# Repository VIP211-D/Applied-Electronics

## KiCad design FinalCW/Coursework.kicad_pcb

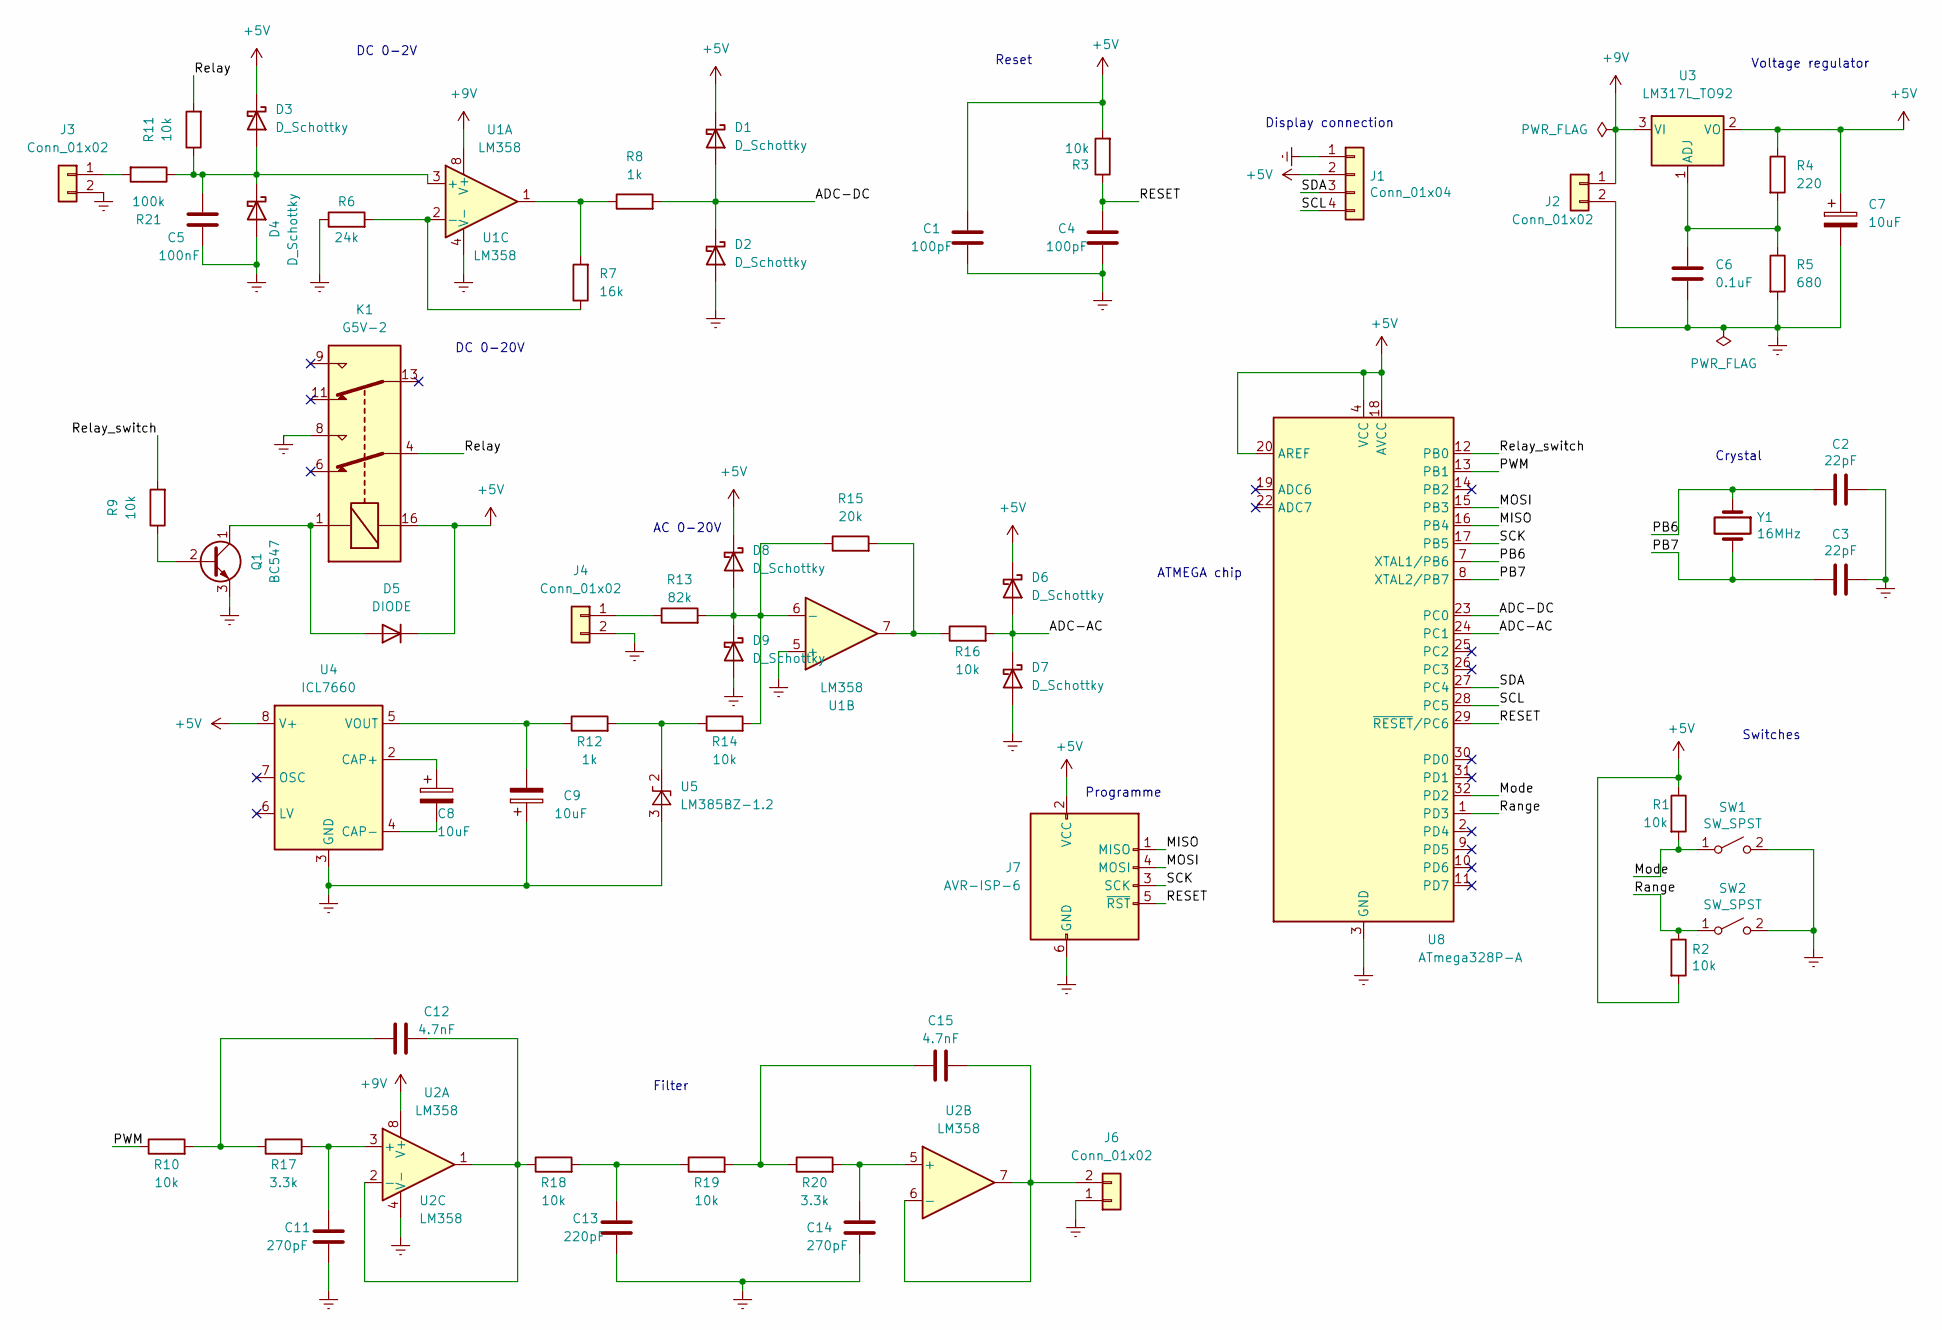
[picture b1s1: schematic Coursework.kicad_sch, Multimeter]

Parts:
C1, C4: 100pF; C_Disc_D3.0mm_W1.6mm_P2.50mm
C2, C3: 22pF; C_0805_2012Metric_Pad1.18x1.45mm_HandSolder
C5: 100nF; C_Disc_D3.0mm_W1.6mm_P2.50mm
C6: 0.1uF; C_Disc_D3.0mm_W1.6mm_P2.50mm
C7, C8, C9: 10uF; CP_Radial_D5.0mm_P2.50mm
C11, C14: 270pF; C_Disc_D3.0mm_W1.6mm_P2.50mm
C12, C15: 4.7nF; C_Disc_D3.0mm_W1.6mm_P2.50mm
C13: 220pF; C_Disc_D3.0mm_W1.6mm_P2.50mm
D1, D2, D3, D4, D6, D7, D8, D9: D_Schottky; D_DO-35_SOD27_P7.62mm_Horizontal
D5: DIODE; D_DO-41_SOD81_P10.16mm_Horizontal
J1: Conn_01x04; PinHeader_1x04_P2.54mm_Horizontal
J2, J3, J4, J6: Conn_01x02; PinHeader_1x02_P2.54mm_Vertical
J7: AVR-ISP-6; PinHeader_2x03_P2.54mm_Vertical
K1: G5V-2; Relay_DPDT_Omron_G5V-2
Q1: BC547; TO-92_Inline
R1, R2, R3, R9, R10, R11, R14, R16, R18, R19: 10k; R_Axial_DIN0207_L6.3mm_D2.5mm_P10.16mm_Horizontal
R4: 220; R_Axial_DIN0207_L6.3mm_D2.5mm_P10.16mm_Horizontal
R5: 680; R_Axial_DIN0207_L6.3mm_D2.5mm_P10.16mm_Horizontal
R6: 24k; R_Axial_DIN0207_L6.3mm_D2.5mm_P10.16mm_Horizontal
R7: 16k; R_Axial_DIN0207_L6.3mm_D2.5mm_P10.16mm_Horizontal
R8, R12: 1k; R_Axial_DIN0207_L6.3mm_D2.5mm_P10.16mm_Horizontal
R13: 82k; R_Axial_DIN0207_L6.3mm_D2.5mm_P10.16mm_Horizontal
R15: 20k; R_Axial_DIN0207_L6.3mm_D2.5mm_P10.16mm_Horizontal
R17, R20: 3.3k; R_Axial_DIN0207_L6.3mm_D2.5mm_P10.16mm_Horizontal
R21: 100k; R_Axial_DIN0207_L6.3mm_D2.5mm_P10.16mm_Horizontal
SW1, SW2: SW_SPST; SW_PUSH_6mm_H5mm
U1, U2: LM358; DIP-8_W7.62mm_LongPads
U3: LM317L_TO92; TO-220-3_Vertical
U4: ICL7660; DIP-8_W10.16mm_LongPads
U5: LM385BZ-1.2; TO-92_Inline
U8: ATmega328P-A; TQFP-32_7x7mm_P0.8mm
Y1: 16MHz; Crystal_SMD_HC49-SD

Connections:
+5V: C1.1, C7.1, D1.1 (K), D3.1 (K), D5.2 (K), D6.1 (K), D8.1 (K), J1.2, J7.2 (VCC), K1.16, R1.1, R2.2, R3.2, R4.1, U3.2 (VO), U4.8 (V+), U8.4 (VCC), U8.6 (VCC), U8.18 (AVCC), U8.20 (AREF)
+9V: J2.1, U1.8 (V+), U2.8 (V+), U3.3 (VI)
/ADC-AC: D6.2 (A), D7.1 (K), R16.2, U8.24 (PC1)
/ADC-DC: D1.2 (A), D2.1 (K), R8.2, U8.23 (PC0)
/MISO: J7.1 (MISO), U8.16 (PB4)
/MOSI: J7.4 (MOSI), U8.15 (PB3)
/Mode: R1.2, SW1.1 (A), U8.32 (PD2)
/PB6: C2.1, U8.7 (XTAL1/PB6), Y1.1
/PB7: C3.1, U8.8 (XTAL2/PB7), Y1.2
/PWM: R10.1, U8.13 (PB1)
/RESET: C4.1, J7.5 (~RST), R3.1, U8.29 (~RESET/PC6)
/Range: R2.1, SW2.1 (A), U8.1 (PD3)
/Relay: K1.4, R11.2
/Relay_switch: R9.2, U8.12 (PB0)
/SCK: J7.3 (SCK), U8.17 (PB5)
/SCL: J1.4, U8.28 (PC5)
/SDA: J1.3, U8.27 (PC4)
Earth: C1.2, C2.2, C3.2, C4.2, C5.2, C6.2, C7.2, C9.1, C11.2, C13.2, C14.2, D2.2 (A), D4.2 (A), D7.2 (A), D9.2 (A), J1.1, J2.2, J3.2, J4.2, J6.1, J7.6 (GND), K1.8, Q1.3 (E), R5.2, R6.1, SW1.2 (B), SW2.2 (B), U1.4 (V-), U1.5 (+), U2.4 (V-), U4.3 (GND), U5.3 (A), U8.3 (GND), U8.5 (GND), U8.21 (GND)
unnamed: C12.1, R10.2, R17.1
unnamed: C13.1, R18.2, R19.1
unnamed: C15.1, R19.2, R20.1
unnamed: C5.1, D3.2 (A), D4.1 (K), R11.1, R21.1, U1.3 (+)
unnamed: D5.1 (A), K1.1, Q1.1 (C)
unnamed: D8.2 (A), D9.1 (K), R13.2, R14.2, R15.1, U1.6 (-)
unnamed: J3.1, R21.2
unnamed: J4.1, R13.1
unnamed: C15.2, J6.2, U2.6 (-), U2.7
unnamed: Q1.2 (B), R9.1
unnamed: R7.2, R8.1, U1.1
unnamed: R15.2, R16.1, U1.7
unnamed: R6.2, R7.1, U1.2 (-)
unnamed: C11.1, R17.2, U2.3 (+)
unnamed: C12.2, R18.1, U2.1, U2.2 (-)
unnamed: C14.1, R20.2, U2.5 (+)
unnamed: C6.1, R4.2, R5.1, U3.1 (ADJ)
unnamed: C8.1, U4.2 (CAP+)
unnamed: C8.2, U4.4 (CAP-)
unnamed: C9.2, R12.1, U4.5 (VOUT)
unnamed: R12.2, R14.1, U5.2 (K)

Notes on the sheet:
DC 0-20V
Switches
Filter
Reset
Crystal
Display connection
AC 0-20V
DC 0-2V
Voltage regulator
ATMEGA chip
Programme

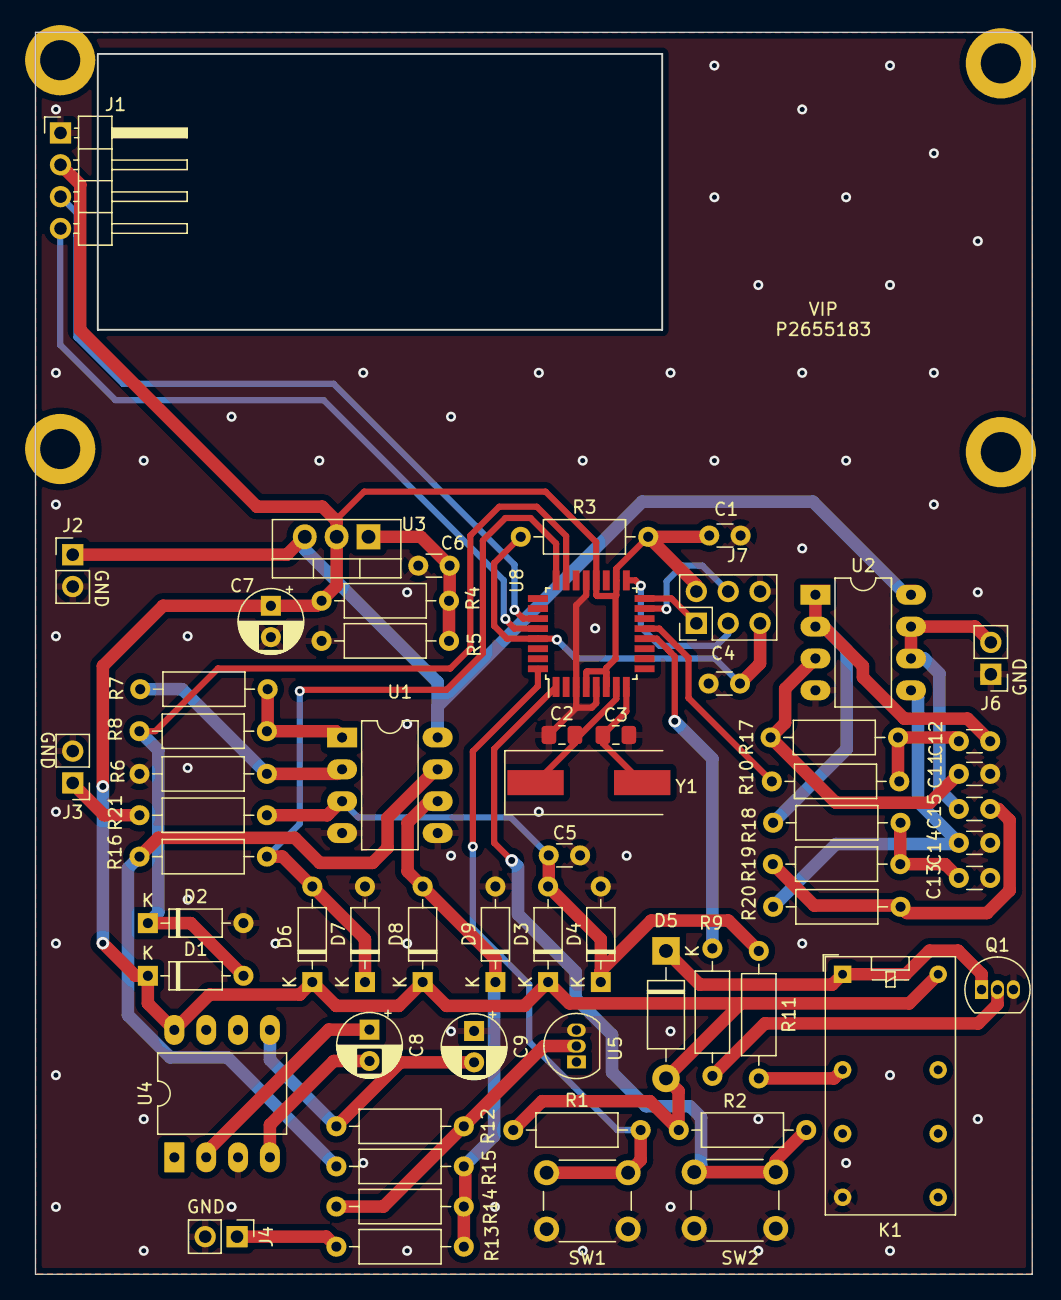
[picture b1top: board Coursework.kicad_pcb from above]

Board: 2 copper layers, 79.4 x 99.0 mm, 61 parts (0 on the bottom side), 39 nets.
